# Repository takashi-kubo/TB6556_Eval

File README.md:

# TB6556_Eval
Evaluation Board schematic for Toshiba 3-Phase Full-Wave Sine-Wave PWM Brushless Motor Controller. 
https://toshiba.semicon-storage.com/info/docget.jsp?did=2160&prodName=TB6556FG

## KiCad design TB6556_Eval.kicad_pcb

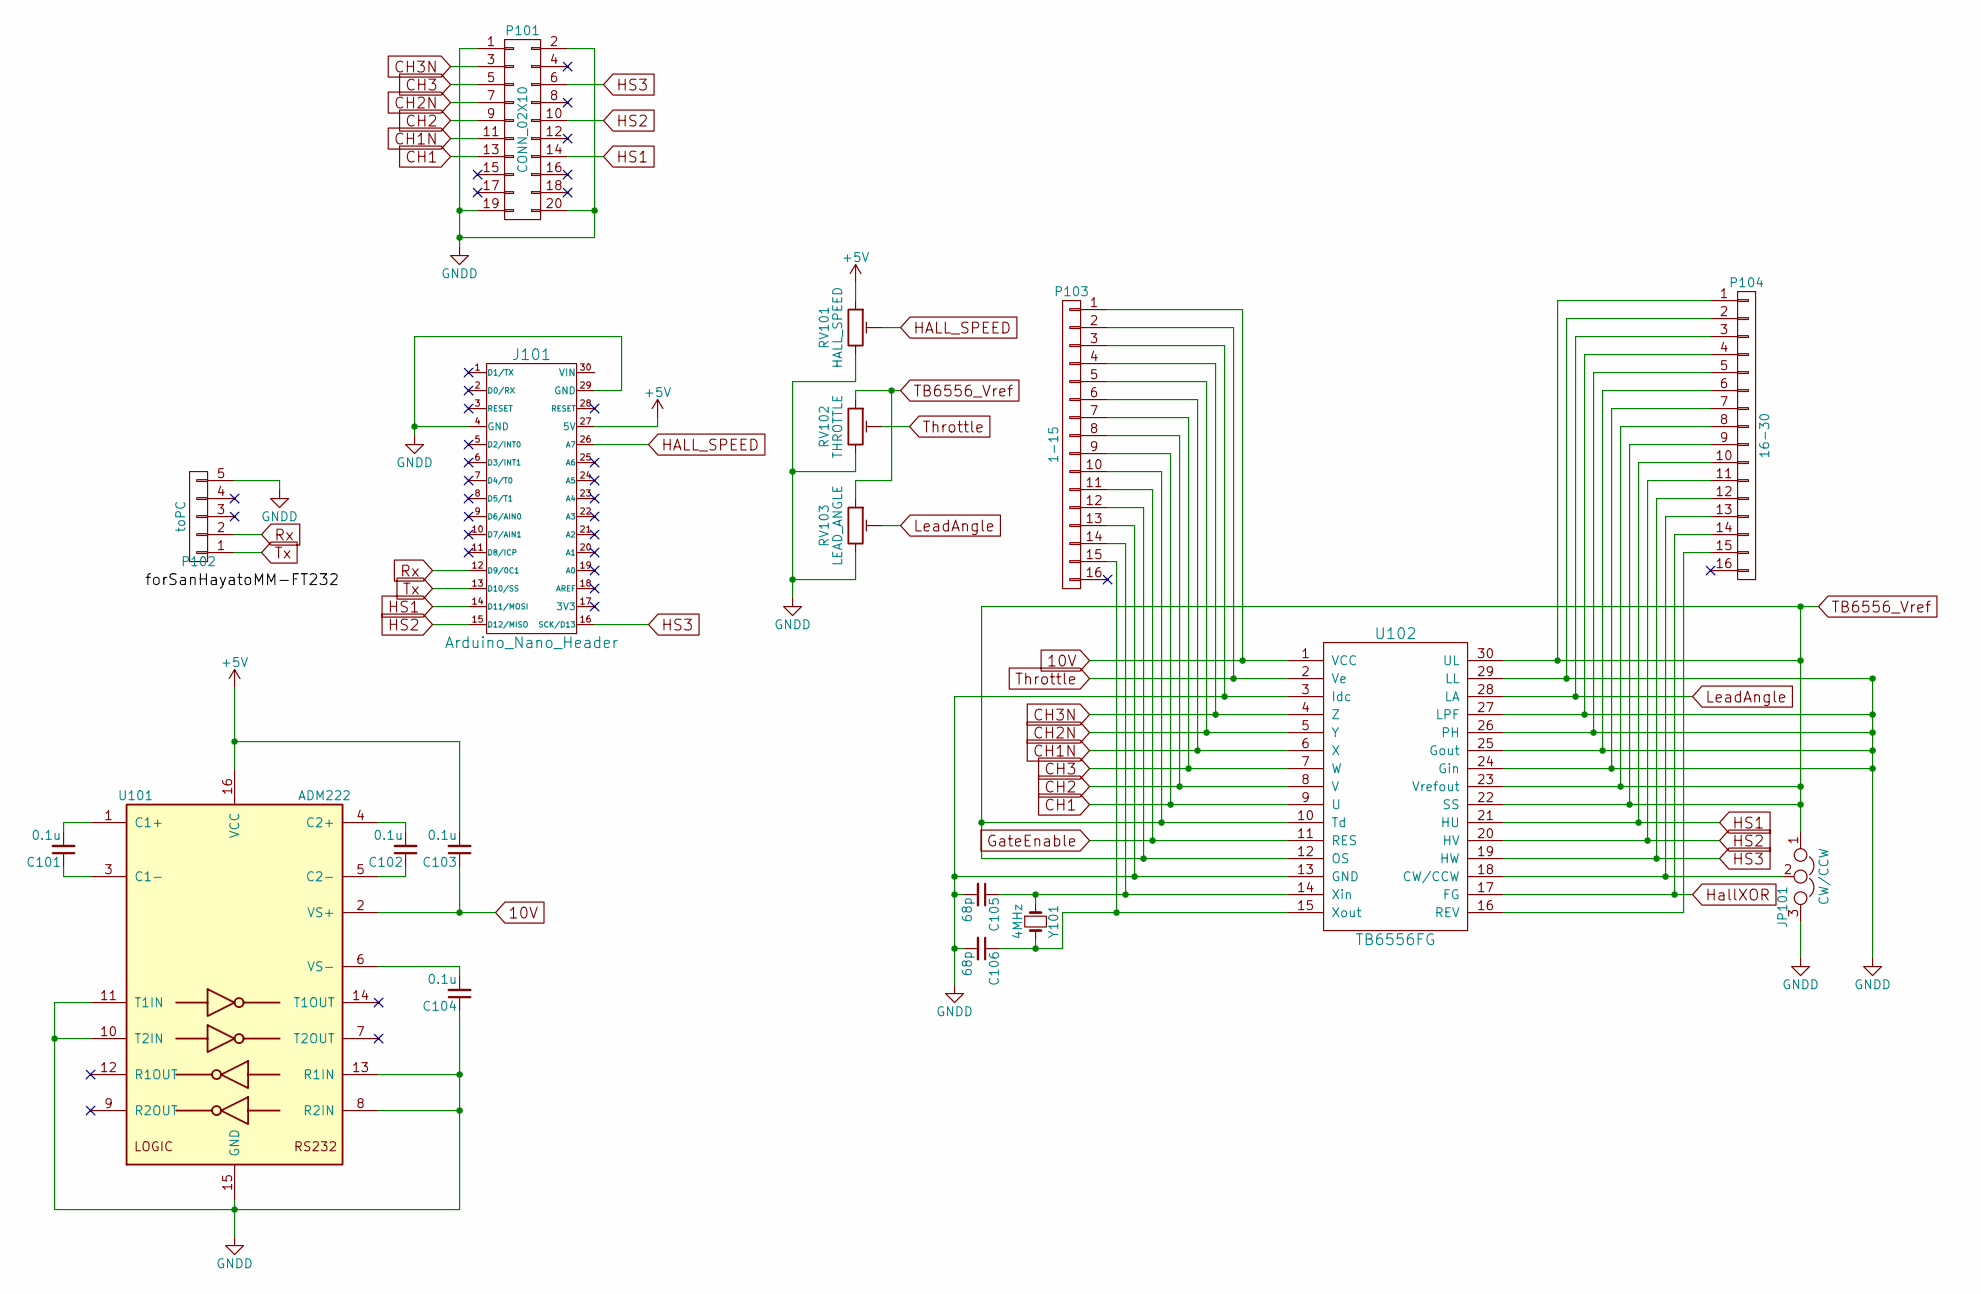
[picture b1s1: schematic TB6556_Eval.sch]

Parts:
C101, C102, C103, C104: 0.1u; C_Rect_L4_W2.5_P2.5
C105, C106: 68p; C_Rect_L4_W2.5_P2.5
J101: Arduino_Nano_Header; arduino_nano_header
JP101: CW/CCW; Pin_Header_Straight_1x03
P101: CONN_02X10; Pin_Header_Straight_2x10
P102: toPC; Pin_Header_Straight_1x05
P103: 1-15; Pin_Header_Straight_2x08
P104: 16-30; Pin_Header_Straight_2x08
RV101: HALL_SPEED; Potentiometer_Bourns_3296Y_3-8Zoll_Angular_ScrewUp
RV102: THROTTLE; Potentiometer_Bourns_3296Y_3-8Zoll_Angular_ScrewUp
RV103: LEAD_ANGLE; Potentiometer_Bourns_3296Y_3-8Zoll_Angular_ScrewUp
U101: ADM222; DIP-16_W7.62mm
U102: TB6556FG; SSOP30-100
Y101: 4MHz; HC-18UV

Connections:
10V: C103.1, P103.1, U101.2 (VS+), U102.1 (VCC)
+5V: C103.2, J101.27 (5V), RV101.1, U101.16 (VCC)
CH1: P101.13, P103.9, U102.9 (U)
CH1N: P101.11, P103.6, U102.6 (X)
CH2: P101.9, P103.8, U102.8 (V)
CH2N: P101.7, P103.5, U102.5 (Y)
CH3: P101.5, P103.7, U102.7 (W)
CH3N: P101.3, P103.4, U102.4 (Z)
GNDD: C104.1, C105.2, C106.2, J101.4 (GND), J101.29 (GND), JP101.3, P101.1, P101.2, P101.19, P101.20, P102.5, P103.3, P103.13, P104.2, P104.4, P104.5, P104.6, P104.7, RV101.3, RV102.3, RV103.3, U101.8 (R2IN), U101.10 (T2IN), U101.11 (T1IN), U101.13 (R1IN), U101.15 (GND), U102.3 (Idc), U102.13 (GND), U102.24 (Gin), U102.25 (Gout), U102.26 (PH), U102.27 (LPF), U102.29 (LL)
GateEnable: P103.11, U102.11 (RES)
HALL_SPEED: J101.26 (A7), RV101.2
HS1: J101.14 (D11/MOSI), P101.14, P104.10, U102.21 (HU)
HS2: J101.15 (D12/MISO), P101.10, P104.11, U102.20 (HV)
HS3: J101.16 (SCK/D13), P101.6, P104.12, U102.19 (HW)
HallXOR: P104.14, U102.17 (FG)
LeadAngle: P104.3, RV103.2, U102.28 (LA)
unnamed: C101.1, U101.3 (C1-)
unnamed: C101.2, U101.1 (C1+)
unnamed: C102.1, U101.5 (C2-)
unnamed: C102.2, U101.4 (C2+)
unnamed: C104.2, U101.6 (VS-)
unnamed: C105.1, P103.14, U102.14 (Xin), Y101.1
unnamed: C106.1, P103.15, U102.15 (Xout), Y101.2
unnamed: JP101.2, P104.13, U102.18 (CW/CCW)
unnamed: P104.15, U102.16 (REV)
Rx: J101.12 (D9/0C1), P102.2
TB6556_Vref: JP101.1, P103.10, P103.12, P104.1, P104.8, P104.9, RV102.1, RV103.1, U102.10 (Td), U102.12 (OS), U102.22 (SS), U102.23 (Vrefout), U102.30 (UL)
Throttle: P103.2, RV102.2, U102.2 (Ve)
Tx: J101.13 (D10/SS), P102.1

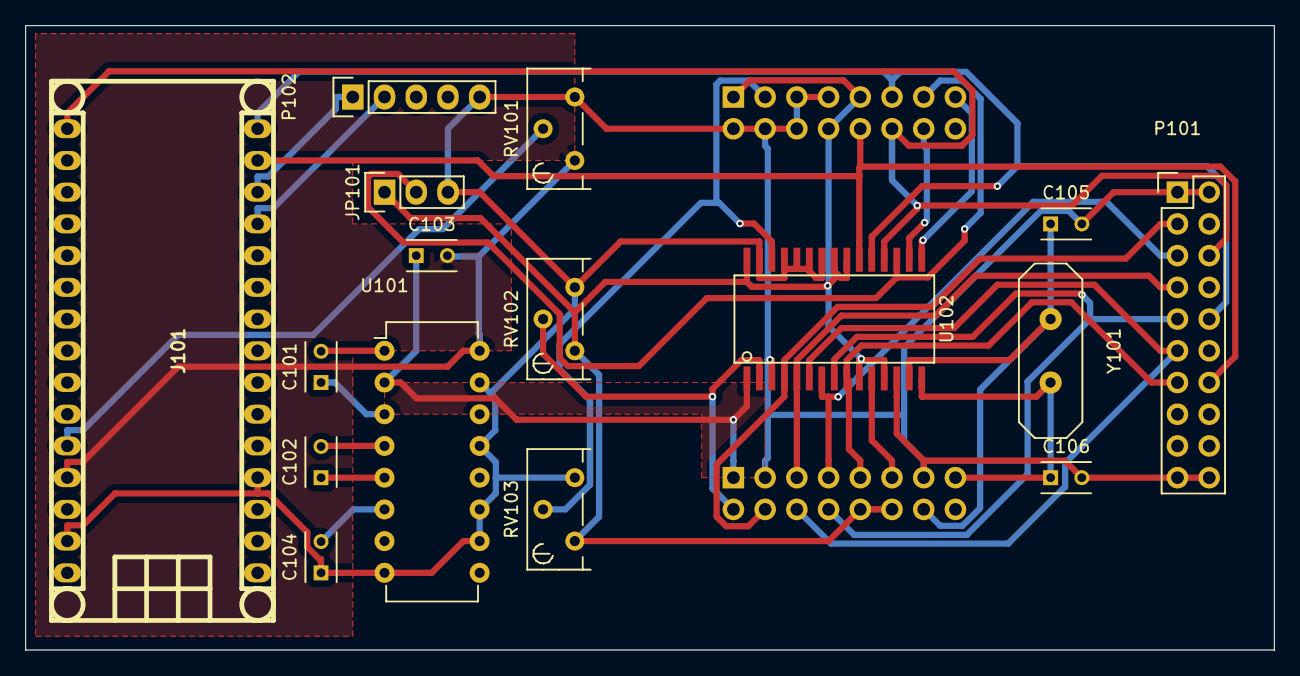
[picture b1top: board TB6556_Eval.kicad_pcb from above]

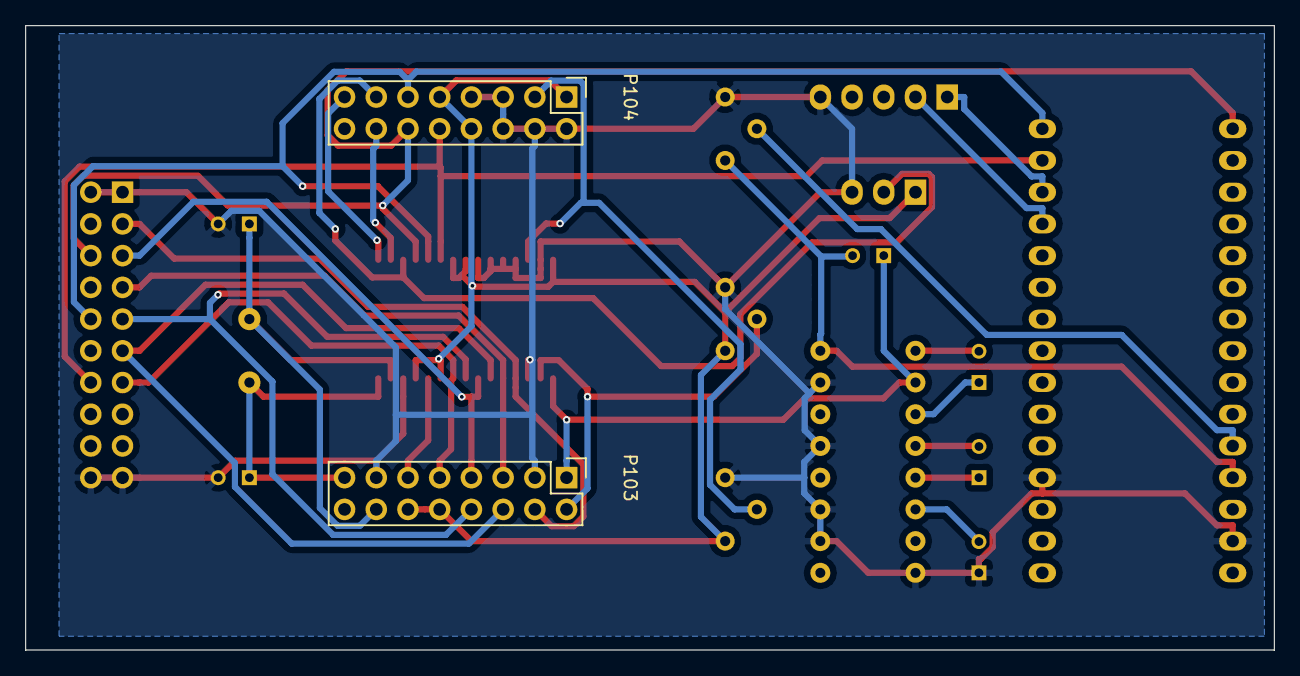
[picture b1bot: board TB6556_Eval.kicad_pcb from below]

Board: 2 copper layers, 100.0 x 50.0 mm, 18 parts (2 on the bottom side), 29 nets.
